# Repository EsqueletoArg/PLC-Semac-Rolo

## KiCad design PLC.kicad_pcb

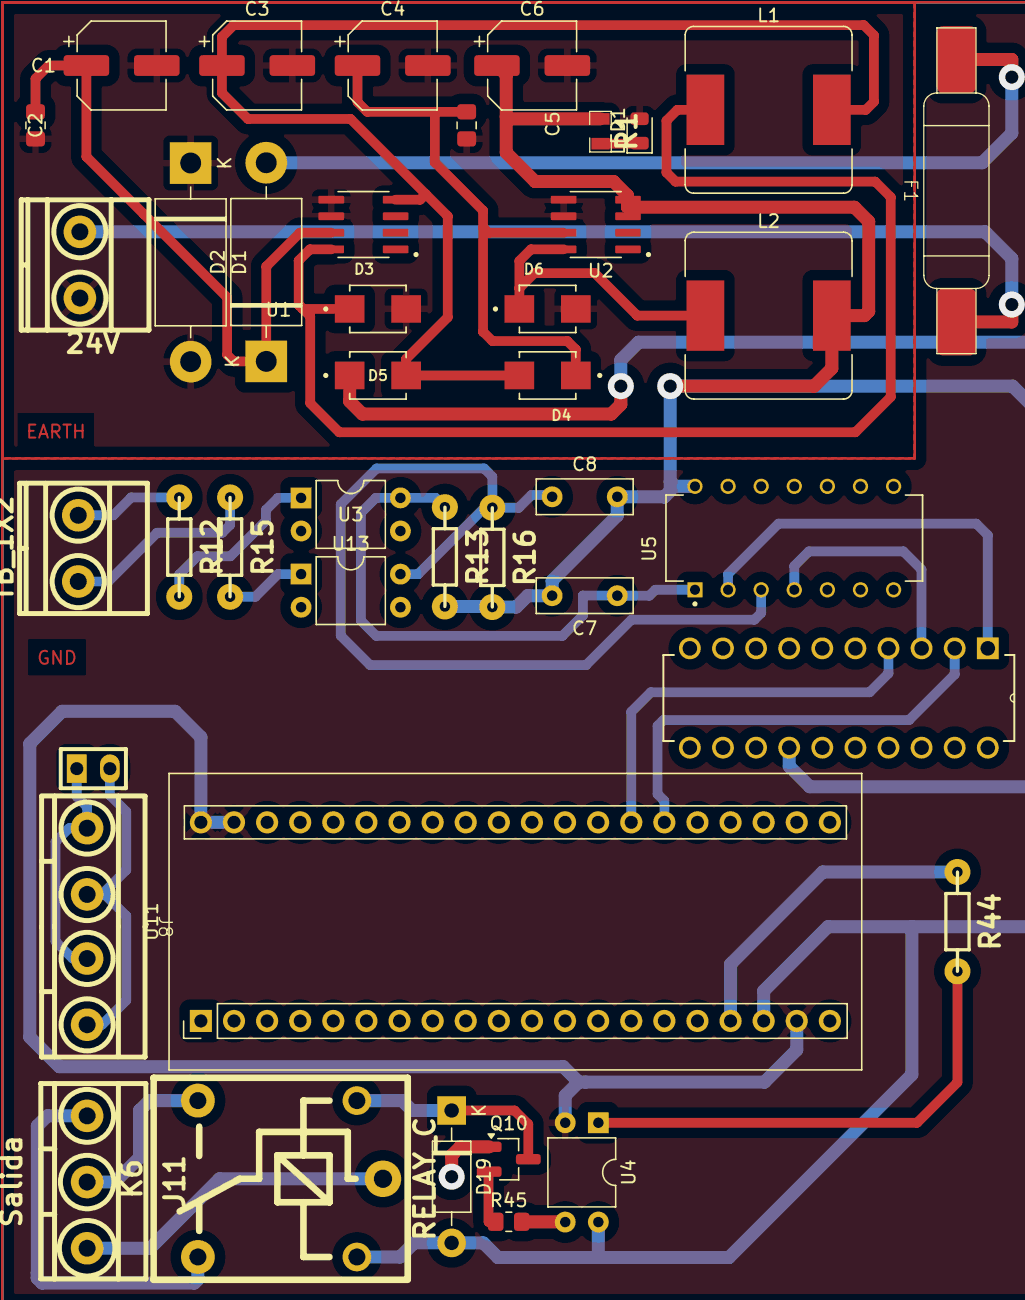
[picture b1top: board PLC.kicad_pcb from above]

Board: 2 copper layers, 41 parts (0 on the bottom side), 36 nets.

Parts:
C1, C4: 470uF; CP_Elec_6.3x7.7
C2, C5: 1uF; C_0805_2012Metric_Pad1.18x1.45mm_HandSolder
C3, C6: 220uF; CP_Elec_6.3x7.7
C7, C8: 100nF; C_Rect_L7.2mm_W2.5mm_P5.00mm_FKS2_FKP2_MKS2_MKP2
D1, D2: 1N5822; D_DO-201AD_P15.24mm_Horizontal
D3, D4, D5, D6: SS210; DIOM4336X265N
D19: 1N4007; D_DO-41_SOD81_P10.16mm_Horizontal
F1: Fuse; Fusible2
J1: 24V; BORNERA2
J8: Screw_Terminal_01x04; Bornera_4
J11: Salida; BORNERA3_AZUL
J13: TB_1X2; BORNERA2
JP1: Jumper; Jumper_Alto
K6: RELAY_C; Relay_C
L1, L2: 68uH; L_Bourns_SRR1260
LED1: LED; LED_0805_2012Metric
Q10: 2N3904; SOT-23_Handsoldering
R1: 1K; R_0805
R12, R13, R15, R16: 10K; RES0.3
R44: 220; RES0.3
R45: 1k; R_0805_2012Metric_Pad1.20x1.40mm_HandSolder
U1: LM2594M-5.0; SOIC127P599X175-8N
U2: LM2594M-3.3; SOIC127P599X175-8N
U3, U4, U13: PC817; DIP-4_W7.62mm
U5: SN74HC14PWR; DIP794W45P254L1969H508Q14
U11: BluePill
U12: SN74HC541PWR; DIP254P762X508-20

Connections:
5V: D5.C, D19.2 (A), K6.5, U4.4, U11.18 (5V)
/1A hc14: C7.1, R13.1, U3.4, U5.1 (1A)
/1Y hc14: U5.2 (1Y), U12.1 (1A)
/2A hc14: C8.1, R16.1, U5.3 (2A), U13.4
/2Y hc14: U5.4 (2Y), U12.3 (2A)
/3Y hc14: U5.6 (3Y), U12.5 (3A)
/4Y hc14: U5.8 (4Y), U12.9 (4A)
/5Y hc14: U5.10 (5Y), U12.11 (5A)
/6Y hc14: U5.12 (6Y), U12.13 (6A)
/IN1: J13.1, R12.1
/IN2: J13.2, R15.1
/PA01: U11.26 (PA1), U12.2 (1Y)
/PA02: U11.27 (PA2), U12.4 (2Y)
/PB09: R44.1, U11.17 (PB9)
/VCC: C6.1, C7.2, C8.2, L2.2, R1.1, R13.2, R16.2, U2.4 (FB), U5.14 (VCC), U12.14 (VCC)
Earth: C1.2, C2.2, C3.2, C4.2, C5.2, C6.2, D1.1 (K), D1.2 (A), D3.A, D6.A, J1.2, LED1.2 (K), Q10.1 (E), U1.5 (ON/OFF), U1.6 (GND), U2.5 (ON/OFF), U2.6 (GND), U3.2, U3.3, U5.7 (GND), U12.7 (GND), U13.2, U13.3
GND: U4.2, U11.19 (GND), U11.39 (GND), U11.40 (GND)
unnamed: D2.2 (A), F1.2
unnamed: C1.1, C2.1, D2.1 (K), U1.7 (VIN)
unnamed: D19.1 (K), K6.2, Q10.3 (C)
unnamed: F1.1, J1.1
unnamed: J8.1 (Pin_3), JP1.1 (A)
unnamed: J8.2 (Pin_4), JP1.2 (B)
unnamed: J11.1, K6.4
unnamed: J11.2, K6.3
unnamed: J11.3, K6.1
unnamed: LED1.1 (A), R1.2
unnamed: Q10.2 (B), R45.1
unnamed: R12.2, U3.1
unnamed: R15.2, U13.1
unnamed: R44.2, U4.1
unnamed: R45.2, U4.3
unnamed: C3.1, D4.A, D5.A, L1.2, U1.4 (FB)
unnamed: D3.C, L1.1, U1.8 (OUT)
unnamed: D6.C, L2.1, U2.8 (OUT)
unnamed: C4.1, C5.1, D4.C, U2.7 (VIN)
